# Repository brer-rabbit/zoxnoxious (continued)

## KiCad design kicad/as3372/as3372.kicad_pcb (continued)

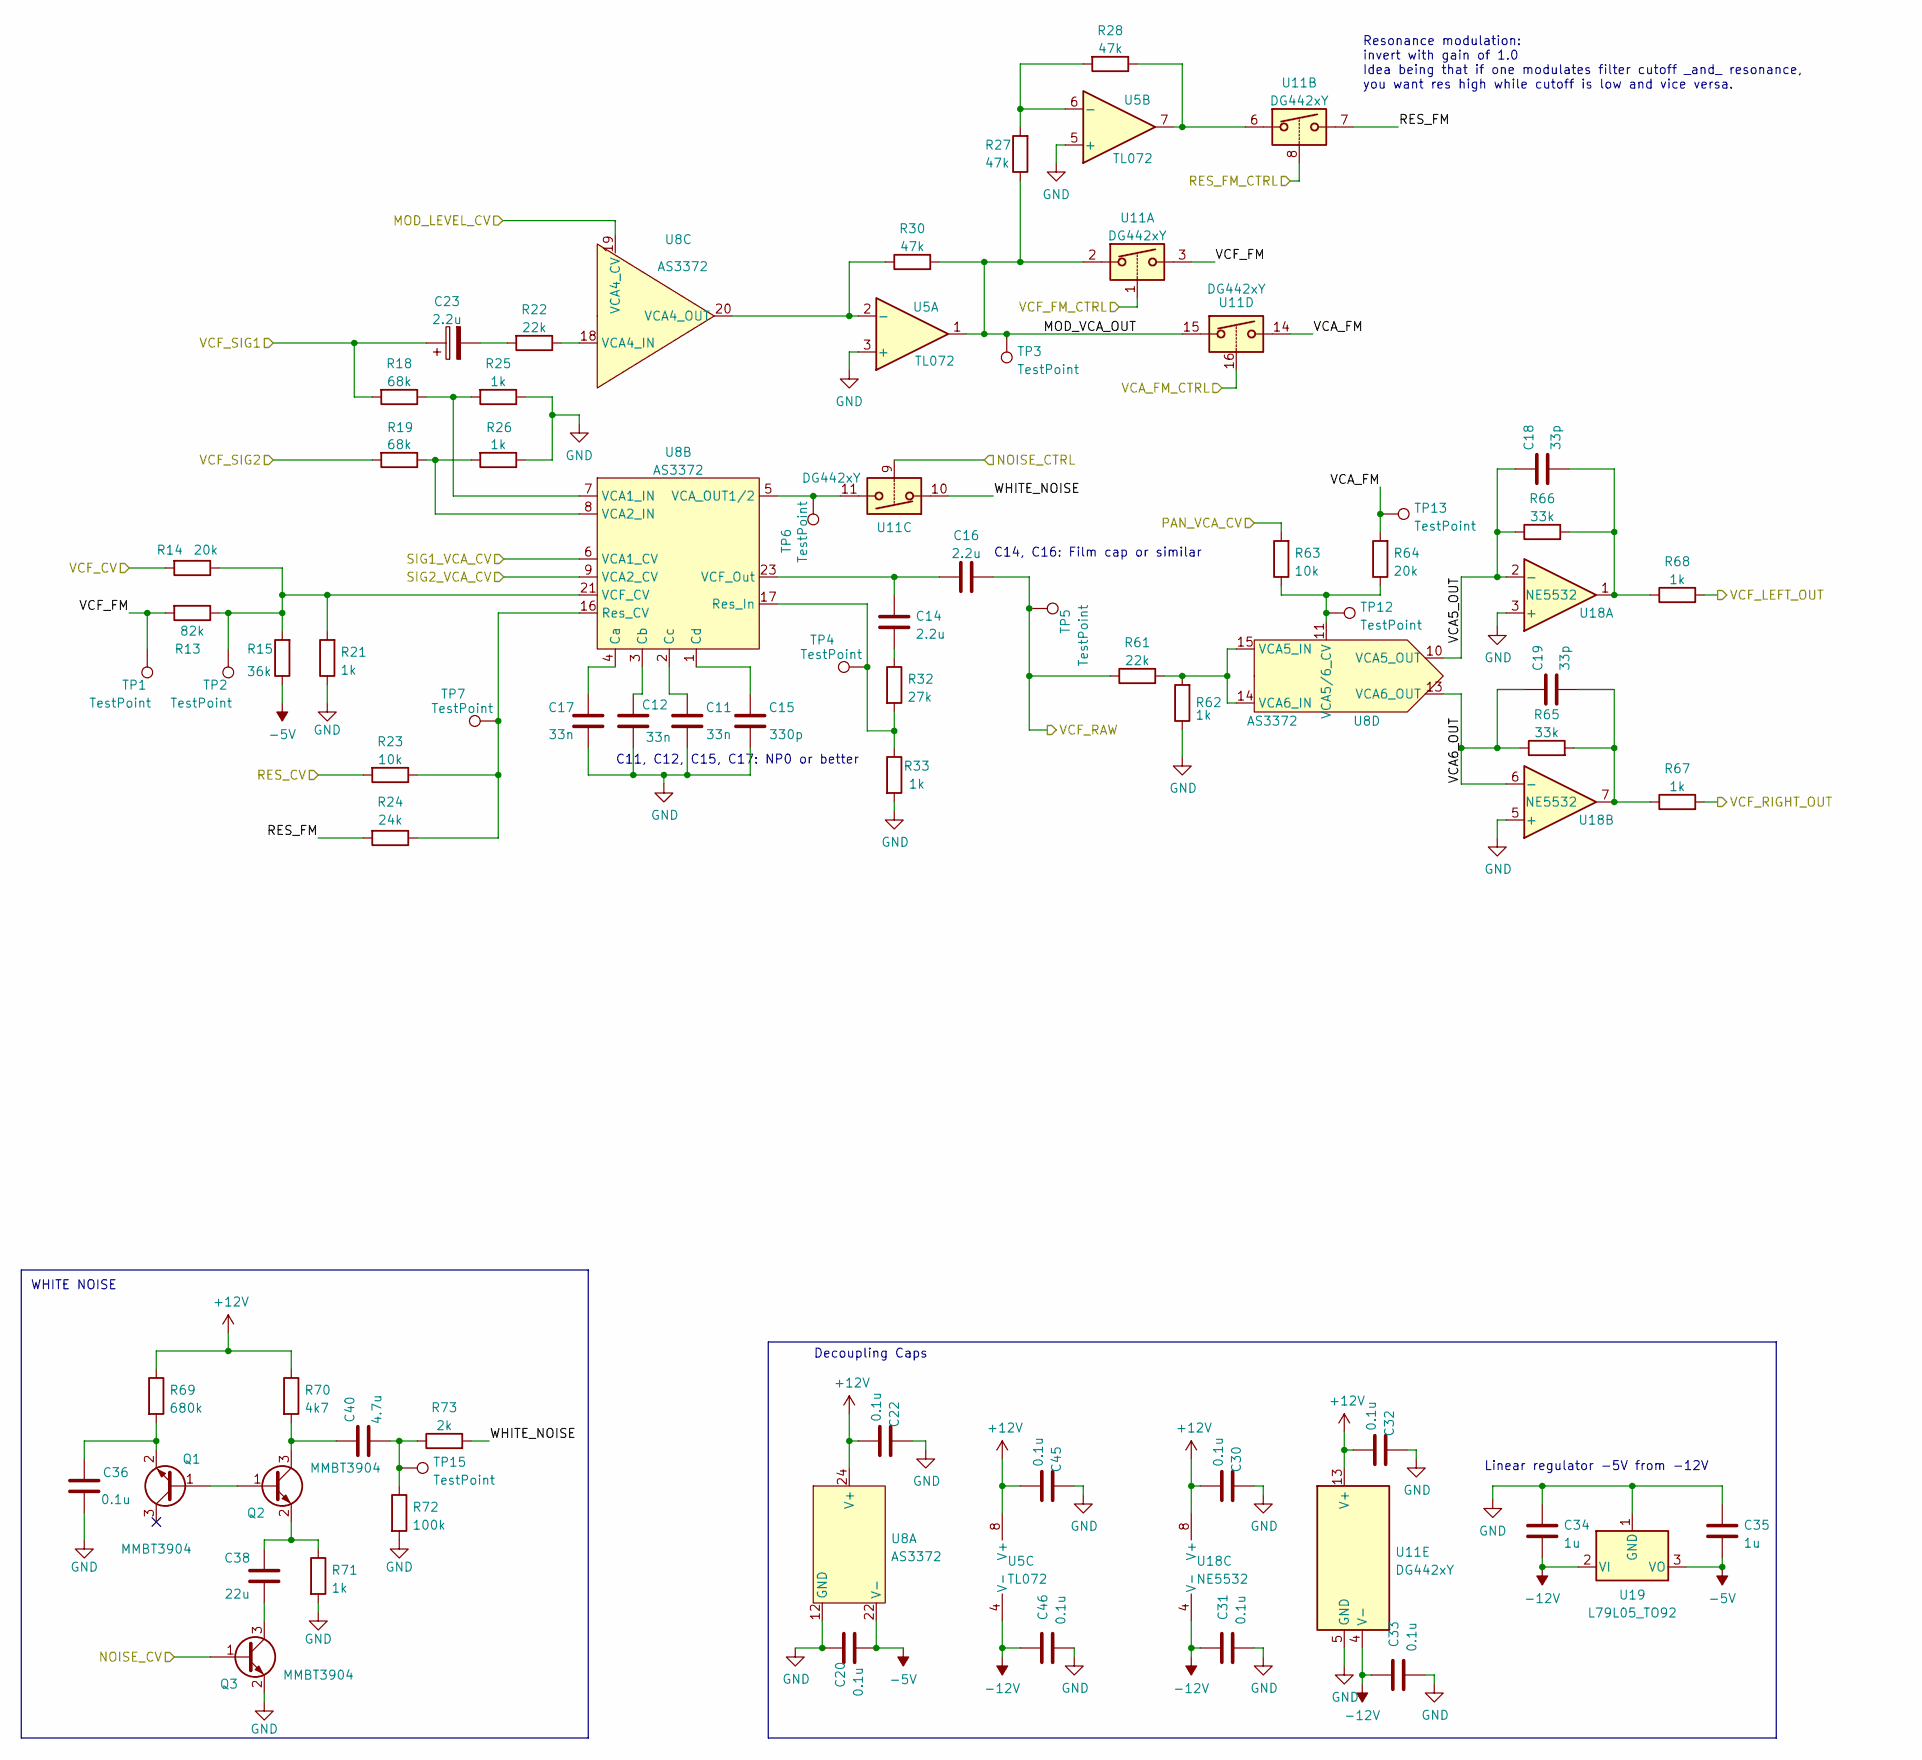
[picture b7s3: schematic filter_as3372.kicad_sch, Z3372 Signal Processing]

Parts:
C11, C12, C17: 33n; C_0805_2012Metric; LCSC Part C342800
C14, C16: 2.2u; C_Rect_L7.2mm_W5.5mm_P5.00mm_FKS2_FKP2_MKS2_MKP2; Digikey MKS2B042201F00KSSD
C15: 330p; C_0805_2012Metric; LCSC Part C694185
C18, C19: 33p; C_0603_1608Metric; LCSC Part C1663
C20, C22, C30, C31, C32, C33, C36, C45, C46: 0.1u; C_0603_1608Metric; LCSC Part C14663
C23: 2.2u; CP_Radial_D4.0mm_P1.50mm; Digikey 1189-4114-ND
C34, C35: 1u; C_0805_2012Metric; LCSC Part C28323
C38: 22u; C_1206_3216Metric; LCSC Part C12891
C40: 4.7u; C_0805_2012Metric; LCSC Part C1779
Q1, Q2, Q3: MMBT3904; SOT-23; LCSC Part C20526
R13: 82k; R_0603_1608Metric; LCSC Part C23254
R14, R64: 20k; R_0603_1608Metric; LCSC Part C4184
R15: 36k; R_0603_1608Metric; LCSC Part C23147
R18, R19: 68k; R_0603_1608Metric; LCSC Part C23231
R21, R25, R26, R33, R62, R67, R68, R71: 1k; R_0603_1608Metric; LCSC Part C21190
R22, R61: 22k; R_0603_1608Metric; LCSC Part C31850
R23, R63: 10k; R_0603_1608Metric; LCSC Part C25804
R24: 24k; R_0603_1608Metric; LCSC Part C23352
R27, R28, R30: 47k; R_0603_1608Metric; LCSC Part C25819
R32: 27k; R_0603_1608Metric; LCSC Part C22967
R65, R66: 33k; R_0603_1608Metric; LCSC Part C4216
R69: 680k; R_0603_1608Metric; LCSC Part C25822
R70: 4k7; R_0603_1608Metric; LCSC Part C23162
R72: 100k; R_0402_1005Metric; LCSC Part C25741
R73: 2k; R_0603_1608Metric; LCSC Part C22975
TP1, TP2, TP3, TP4, TP5, TP6, TP7, TP12, TP13, TP15: TestPoint; TestPoint_Pad_2.0x2.0mm
U5: TL072; SOIC-8_3.9x4.9mm_P1.27mm; LCSC Part C6961
U8: AS3372; SOIC-24W_7.5x15.4mm_P1.27mm
U11: DG442xY; SOIC-16_3.9x9.9mm_P1.27mm; LCSC Part C144269
U18: NE5532; SOIC-8_3.9x4.9mm_P1.27mm; LCSC Part C7426
U19: L79L05_TO92; TO-92_Inline_Wide

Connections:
+12V: C22.2, C30.2, C32.2, C45.2, R69.1, R70.1, U5.8 (V+), U8.24 (V+), U11.13 (V+), U18.8 (V+); also elsewhere on the board
-5V: C20.2, C35.2, R15.1, U8.22 (V-), U19.3 (VO)
-12V: C31.1, C33.1, C34.2, C46.1, U5.4 (V-), U11.4 (V-), U18.4 (V-), U19.2 (VI); also elsewhere on the board
/DAC/MOD_AMOUNT_VCA3_CV: U8.19 (VCA4_CV); also elsewhere on the board
/DAC/NOISE_CONTROL_CV: Q3.1 (B); also elsewhere on the board
/DAC/PAN_VCA_CV: R63.2; also elsewhere on the board
/DAC/RESONANCE_CV: R23.2; also elsewhere on the board
/DAC/SIG1_VCA1_CV: U8.6 (VCA1_CV); also elsewhere on the board
/DAC/SIG2_VCA2_CV: U8.9 (VCA2_CV); also elsewhere on the board
/DAC/VCF_CV: R14.2; also elsewhere on the board
/RES_FM_CTRL: U11.8; also elsewhere on the board
/THIS_OUT1: R68.2; also elsewhere on the board
/THIS_OUT2: R67.2; also elsewhere on the board
/VCA_FM_CTRL: U11.16; also elsewhere on the board
/VCF_FM_CTRL: U11.1; also elsewhere on the board
/VCF_RAW: C16.2, R61.1, TP5.1; also elsewhere on the board
/VCF_SIGNAL1: C23.1, R18.2; also elsewhere on the board
/VCF_SIGNAL2: R19.2; also elsewhere on the board
/WHITE_NOISE_CTRL: U11.9; also elsewhere on the board
/filter_as3372/MOD_VCA_OUT: R27.1, R30.2, TP3.1, U5.1, U11.2, U11.15
/filter_as3372/RES_FM: R24.2, U11.7
/filter_as3372/VCA5_OUT: C18.1, R66.1, U8.10 (VCA5_OUT), U18.2 (-)
/filter_as3372/VCA6_OUT: C19.1, R65.1, U8.13 (VCA6_OUT), U18.6 (-)
/filter_as3372/VCA_FM: R64.2, TP13.1, U11.14
/filter_as3372/VCF_FM: R13.2, TP1.1, U11.3
/filter_as3372/WHITE_NOISE: R73.2, U11.10
GND: C11.2, C12.2, C15.2, C17.1, C20.1, C22.1, C30.1, C31.2, C32.1, C33.2, C34.1, C35.1, C36.2, C45.1, C46.2, Q3.2 (E), R21.1, R25.1, R26.1, R33.2, R62.1, R71.2, R72.2, U5.3 (+), U5.5 (+), U8.12 (GND), U11.5 (GND), U18.3 (+), U18.5 (+), U19.1 (GND); also elsewhere on the board
unnamed: C11.1, U8.2 (Cc)
unnamed: C12.1, U8.3 (Cb)
unnamed: C14.1, C16.1, U8.23 (VCF_Out)
unnamed: C14.2, R32.1
unnamed: C15.1, U8.1 (Cd)
unnamed: C17.2, U8.4 (Ca)
unnamed: C18.2, R66.2, R68.1, U18.1
unnamed: C19.2, R65.2, R67.1, U18.7
unnamed: C23.2, R22.2
unnamed: C36.1, Q1.2 (E), R69.2
unnamed: C38.1, Q2.2 (E), R71.1
unnamed: C38.2, Q3.3 (C)
unnamed: C40.1, Q2.3 (C), R70.2
unnamed: C40.2, R72.1, R73.1, TP15.1
unnamed: Q1.1 (B), Q2.1 (B)
unnamed: R13.1, R14.1, R15.2, R21.2, TP2.1, U8.21 (VCF_CV)
unnamed: R18.1, R25.2, U8.7 (VCA1_IN)
unnamed: R19.1, R26.2, U8.8 (VCA2_IN)
unnamed: R22.1, U8.18 (VCA4_IN)
unnamed: R23.1, R24.1, TP7.1, U8.16 (Res_CV)
unnamed: R27.2, R28.2, U5.6 (-)
unnamed: R28.1, U5.7, U11.6
unnamed: R30.1, U5.2 (-), U8.20 (VCA4_OUT)
unnamed: R32.2, R33.1, TP4.1, U8.17 (Res_In)
unnamed: R61.2, R62.2, U8.14 (VCA6_IN), U8.15 (VCA5_IN)
unnamed: R63.1, R64.1, TP12.1, U8.11 (VCA5/6_CV)
unnamed: TP6.1, U8.5 (VCA_OUT1/2), U11.11

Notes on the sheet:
Resonance modulation: invert with gain of 1.0 Idea being that if one modulates filter cutoff _and_ resonance, you want res high while cutoff is low and vice versa.
Decoupling Caps
C14, C16: Film cap or similar
WHITE NOISE
Linear regulator -5V from -12V
C11, C12, C15, C17: NP0 or better

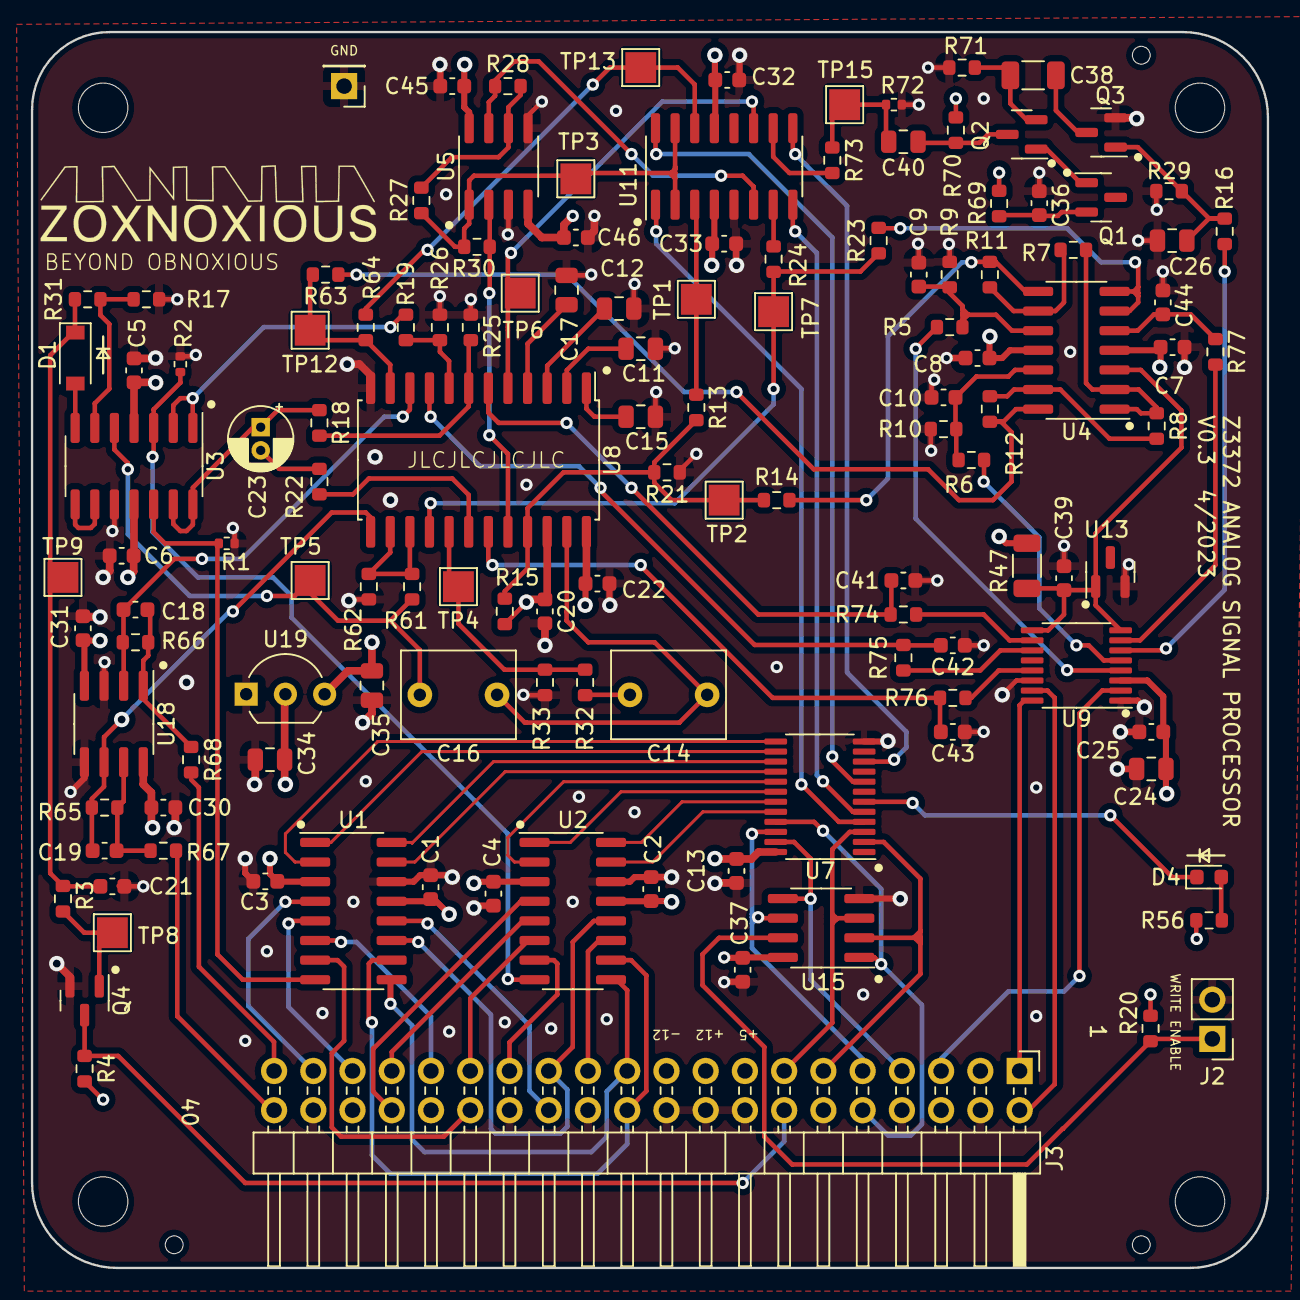
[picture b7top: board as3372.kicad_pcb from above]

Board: 4 copper layers, 80.0 x 80.0 mm, 133 parts (0 on the bottom side), 109 nets.

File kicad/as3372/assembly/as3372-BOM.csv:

Comment,Designator,Footprint,LCSC Part #
0.1u Unpolarized capacitor,"C1,C2,C3,C4,C5,C6,C7,C8,C13,C20,C21,C22,C25,C30,C31,C32,C33,C36,C37,C39,C45,C46",C_0603_1608Metric,C14663
68n Unpolarized capacitor,C9,C_0603_1608Metric,C31658
10n Unpolarized capacitor,"C10,C41,C42,C43,C44",C_0603_1608Metric,C57112
33n Unpolarized capacitor,"C11,C12,C17",C_0805_2012Metric,C342800
2.2u Unpolarized capacitor,"C14,C16",C_Rect_L7.2mm_W5.5mm_P5.00mm_FKS2_FKP2_MKS2_MKP2,
330p Unpolarized capacitor,C15,C_0805_2012Metric,C694185
33p Unpolarized capacitor,"C18,C19",C_0603_1608Metric,C1663
2.2u Polarized capacitor,C23,CP_Radial_D4.0mm_P1.50mm,
4.7u Unpolarized capacitor,"C24,C40",C_0805_2012Metric,C1779
22n Unpolarized capacitor,C26,C_0805_2012Metric,C21122
1u Unpolarized capacitor,"C34,C35",C_0805_2012Metric,C28323
22u Unpolarized capacitor,C38,C_1206_3216Metric,C12891
"1N4148W 75V 0.15A Fast Switching Diode, SOD-123",D1,D_SOD-123,C81598
LED Light emitting diode,D4,LED_0603_1608Metric,C2286
MountingHole Mounting Hole without connection,"H1,H2,H3,H4",MountingHole_3.2mm_M3,
"Conn_01x01 Generic connector, single row, 01x01, script generated (kicad-library-utils/schlib/autogen/connector/)",J1,PinHeader_1x01_P2.54mm_Vertical,
"Conn_01x02 Generic connector, single row, 01x02, script generated (kicad-library-utils/schlib/autogen/connector/)",J2,PinHeader_1x02_P2.54mm_Vertical,
"Conn_02x20_Odd_Even Generic connector, double row, 02x20, odd/even pin numbering scheme (row 1 odd numbers, row 2 even numbers), script generated (kicad-library-utils/schlib/autogen/connector/)",J3,PinHeader_2x20_P2.54mm_Horizontal,
"MMBT3904 0.2A Ic, 40V Vce, Small Signal NPN Transistor, SOT-23","Q1,Q2,Q3,Q4",SOT-23,C20526
100k Resistor,"R1,R2,R72",R_0402_1005Metric,C25741
4k7 Resistor,"R3,R20,R70",R_0603_1608Metric,C23162
10k Resistor,"R4,R23,R63",R_0603_1608Metric,C25804
2k4 Resistor,R5,R_0603_1608Metric,C22940
20k Resistor,"R6,R8,R10,R12,R14,R64",R_0603_1608Metric,C4184
8k2 Resistor,R7,R_0603_1608Metric,C25981
120k Resistor,R9,R_0603_1608Metric,C25808
3k3 Resistor,R11,R_0603_1608Metric,C22978
82k Resistor,R13,R_0603_1608Metric,C23254
36k Resistor,R15,R_0603_1608Metric,C23147
18k Resistor,R16,R_0603_1608Metric,C25810
100k Resistor,R17,R_0603_1608Metric,C25803
68k Resistor,"R18,R19",R_0603_1608Metric,C23231
1k Resistor,"R21,R25,R26,R33,R62,R67,R68,R71",R_0603_1608Metric,C21190
22k Resistor,"R22,R61",R_0603_1608Metric,C31850
24k Resistor,R24,R_0603_1608Metric,C23352
47k Resistor,"R27,R28,R30,R31",R_0603_1608Metric,C25819
9k1 Resistor,R29,R_0603_1608Metric,C23260
27k Resistor,R32,R_0603_1608Metric,C22967
4k7 Resistor,R47,R_1206_3216Metric,C17936
2k Resistor,"R56,R73",R_0603_1608Metric,C22975
33k Resistor,"R65,R66",R_0603_1608Metric,C4216
680k Resistor,R69,R_0603_1608Metric,C25822
15k Resistor,"R74,R75,R76,R77",R_0603_1608Metric,C22809
TestPoint test point,"TP1,TP2,TP3,TP4,TP5,TP6,TP7,TP8,TP9,TP12,TP13,TP15",TestPoint_Pad_2.0x2.0mm,
MUX508 ,"U1,U2",SOIC-16_3.9x9.9mm_P1.27mm,C2673104
"TL074 Quad Low-Noise JFET-Input Operational Amplifiers, DIP-14/SOIC-14","U3,U4",SOIC-14_3.9x8.7mm_P1.27mm,C12594
"TL072 Dual Low-Noise JFET-Input Operational Amplifiers, DIP-8/SOIC-8",U5,SOIC-8_3.9x4.9mm_P1.27mm,C6961
"CAT9555YI-T2 IO expander 16 GPIO, I2C 400kHz, Interrupt, 2.3 - 5.5V, SOIC-24",U7,TSSOP-24_4.4x7.8mm_P0.65mm,C83265
AS3372 AS 3372 Signal Processor,U8,SOIC-24W_7.5x15.4mm_P1.27mm,
AD5328 Octal Voltage Output DAC,U9,TSSOP-16_4.4x5mm_P0.65mm,C29162
"DG442xY Quad SPST Analog Switches, normally OFF, 60Ohm Ron, SOIC-16",U11,SOIC-16_3.9x9.9mm_P1.27mm,C144269
"LM4040AIM3-2.5 2.500V Precision Micropower Shunt Voltage Reference, SOT-23",U13,SOT-23,C460725
"M24C02-WMN 2Kb (256x8) I2C Serial EEPROM, 2.5-5.5V, SOIC-8",U15,SOIC-8_3.9x4.9mm_P1.27mm,C7562
"NE5532 Dual Low-Noise Operational Amplifiers, DIP-8/SOIC-8",U18,SOIC-8_3.9x4.9mm_P1.27mm,C7426
"L79L05_TO92 Negative 100mA -30V Linear Regulator, Fixed Output -5V, TO-92",U19,TO-92_Inline_Wide,

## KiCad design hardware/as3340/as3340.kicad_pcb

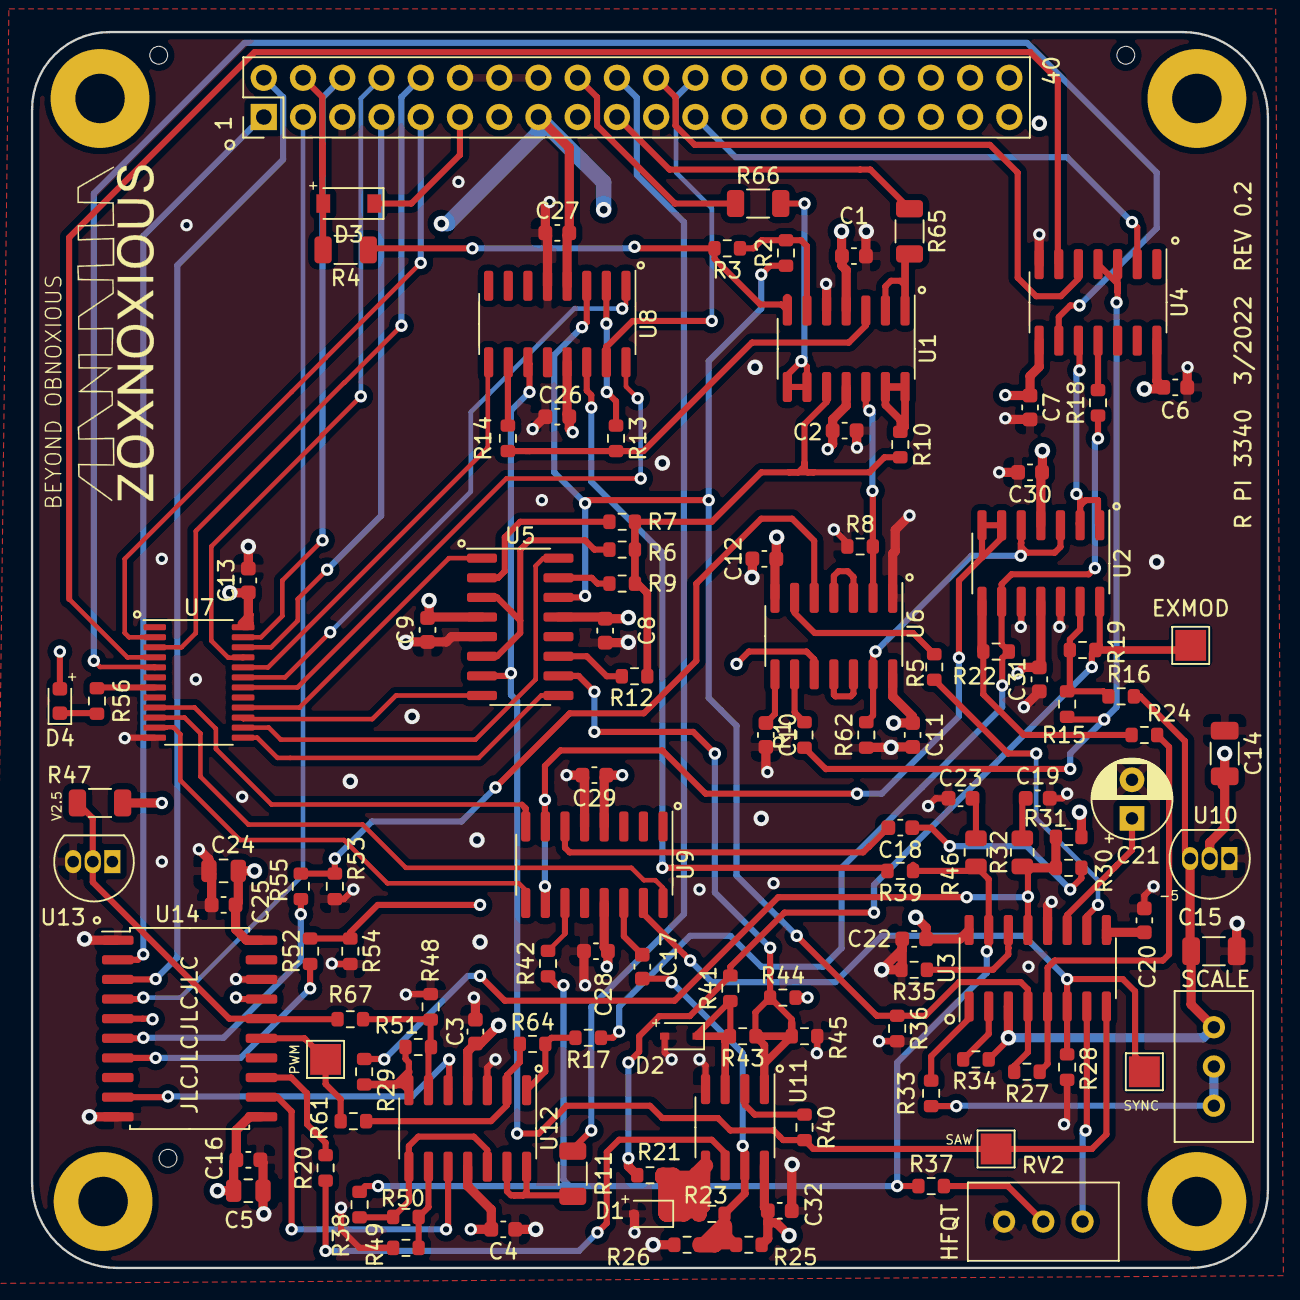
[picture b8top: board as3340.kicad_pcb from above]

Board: 4 copper layers, 80.0 x 80.0 mm, 123 parts (0 on the bottom side), 106 nets.

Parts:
C1, C2, C3, C4, C6, C7, C8, C9, C11, C12, C13, C22, C26, C27, C28, C29, C30, C31, C32: 0.1u; C_0603_1608Metric
C5, C24: 4.7u; C_0805_2012Metric
C10: 4.7n; C_0603_1608Metric
C14, C15: 1u; C_1206_3216Metric
C16, C20, C25: 100n; C_0603_1608Metric
C17: 1u; C_0603_1608Metric
C18, C19, C23: 10n; C_0603_1608Metric
C21: 1000p; CP_Radial_D5.0mm_P2.50mm
D1, D2: 1N5819; D_SOD-323
D3: 1N4148W; D_SOD-123
D4: LED; LED_0603_1608Metric
H1, H2, H3, H4: MountingHole; MountingHole_3.2mm_M3_Pad
J1: Conn_02x20_Odd_Even; PinHeader_2x20_P2.54mm_Vertical
R1, R2, R5, R6: 47k; R_0603_1608Metric
R3, R18, R48, R51: 100k; R_0603_1608Metric
R4, R11, R65, R66: 1k; R_1206_3216Metric
R7, R12, R14, R54, R55, R64: 20k; R_0603_1608Metric
R8, R62, R67: 51k; R_0603_1608Metric
R9, R13: 27k; R_0603_1608Metric
R10, R20, R21, R24, R28, R40, R41, R61: 10k; R_0603_1608Metric
R15, R16: 68k; R_0603_1608Metric
R17, R22: 56k; R_0603_1608Metric
R19: 33k; R_0603_1608Metric
R23, R27, R29, R30, R37, R43: 1M; R_0603_1608Metric
R25, R26, R34: 5k6; R_0603_1608Metric
R31: 1.5M; R_0603_1608Metric
R32, R46: 470; R_0805_2012Metric
R33: 20K; R_0603_1608Metric
R35: 1K82; R_0603_1608Metric
R36: 51K; R_0603_1608Metric
R38, R39: 100k 0.1%; R_0603_1608Metric
R42: 300k; R_0603_1608Metric
R44: 18k; R_0603_1608Metric
R45: 13k; R_0603_1608Metric
R47: 4k7; R_1206_3216Metric
R49: 10k .1%; R_0603_1608Metric
R50: 30k .1%; R_0603_1608Metric
R52, R53: 30k; R_0603_1608Metric
R56: 2k; R_0603_1608Metric
RV1: 10K; Potentiometer_Bourns_3296W_Vertical
RV2: 20k; Potentiometer_Bourns_3296W_Vertical
TP1, TP2, TP3, TP4: TestPoint; TestPoint_Pad_2.0x2.0mm
U1, U2, U12: TL074; SOIC-14_3.9x8.7mm_P1.27mm
U3: AS3340; SOIC-16_3.9x9.9mm_P1.27mm
U4: DG303B; SOIC-14_3.9x8.7mm_P1.27mm
U5, U8, U9: DG442CY+; SOIC-16_3.9x9.9mm_P1.27mm
U6: AS3360; SOIC-14_3.9x8.7mm_P1.27mm
U7: PCA9555D; TSSOP-24_4.4x7.8mm_P0.65mm
U10: LM79L05; TO-92_Inline
U11: LM393; SOIC-8_3.9x4.9mm_P1.27mm
U13: LM4040AIM3-5.0; TO-92L_Inline
U14: TLV5610IDW; SOIC-20W_7.5x12.8mm_P1.27mm

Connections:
+5V: C5.1, C13.1, C16.1, C24.2, C25.2, D3.1, D4.2, J1.11, R47.1, U7.24, U14.5, U14.11, U14.17, U14.20
+12V: C1.1, C3.1, C6.1, C8.1, C11.1, C22.2, C26.1, C28.1, C30.1, C32.1, J1.13, R25.2, R31.1, R44.2, U1.4, U2.4, U3.16, U4.14, U5.13, U6.14, U8.13, U9.13, U11.8, U12.4
-5V: C15.2, R16.2, R34.2, RV1.3, U3.3, U10.3
-12V: C2.2, C4.2, C7.2, C9.2, C12.2, C14.2, C27.2, C29.2, C31.2, J1.15, U1.11, U2.11, U4.8, U5.4, U6.7, U8.4, U9.4, U10.2, U12.11
/DAC/FREQ_CV_FROM_DAC: U12.10, U14.12
/DAC/LINEAR_FM_FROM_DAC: U12.5, U14.9
/DAC/OSC_EXT_VCA_FROM_DAC: R52.2, U14.7
/DAC/PWM_FROM_DAC: R61.2, TP1.1, U14.15
/DAC/TRI_VCA_FROM_DAC: R53.2, U14.6
/DAC/VREF_2.5V: R47.2, R67.2, U13.2, U14.16
/EXP_FM_EXT_CTRL: U7.11, U9.9
/EXT_CV: J1.24, U8.15
/EXT_FREQ_CV_CTRL: U7.18, U8.16
/EXT_MOD_PW_CTRL: U4.9, U7.5
/EXT_MOD_SEL_CTRL: U4.6, U7.4
/EXT_OSC_MOD: R1.1, R15.2, U4.3, U4.4
/EXT_OSC_VCA_AMOUNT: R52.1, R54.2, U6.10
/GPIO_MODULE_DRIVEN: D3.2, J1.4, R4.2
/GPIO_PI_DRIVEN: J1.3, U14.4
/HARD_SYNC_CTRL: U7.10, U9.16
/I2C_ADDR0: J1.8, U7.21
/I2C_ADDR1: J1.9, U7.2
/I2C_ADDR2: J1.10, U7.3
/LED_CTRL: R56.2, U7.7
/LINEAR_FM_DAC: R29.2, R51.1, U12.7
/LINEAR_FM_EXT_CTRL: U7.9, U9.8
/MIX1_COMP_OSC2_CTRL: U5.9, U7.13
/MIX1_PULSE_CTRL: U5.16, U7.14
/MIX1_SAW_CTRL: U5.8, U7.15
/MIX2_PULSE_CTRL: U7.19, U8.1
/MIX2_SAW_CTRL: U7.20, U8.9
/OSC1_CV: J1.20, R11.2
/OSC1_CV_DAC: R38.2, R50.1, U12.8, U12.12
/OSC1_MIX1: J1.18, R66.2
/OSC1_MIX2: J1.19, R65.2
/OSC2_MIX1: J1.22, U4.5
/OSC2_MIX2: J1.23, U4.2
/Output Mix/MIX1_SUM: R6.2, R7.2, R9.2, R10.2, R12.2, U1.10
/Output Mix/SCALED_TRI: R10.1, U1.13, U1.14
/Output Mix/VCA_TRI: R8.2, U1.12, U6.2
/PWM_DAC: R17.2, R64.1, U12.1
/SAW_LEVEL_CTRL: U5.1, U7.16
/SCL1: J1.7, U7.22
/SDA1: J1.6, U7.23
/SPI0_MOSI: J1.1, U14.2
/SPI0_SCLK: J1.2, U14.3
/SYNC_LEVEL_DAC: R20.2, U14.13
/TRI_VC_AMOUNT_DAC: R53.1, R55.2, U6.5
/VCO_COMP: R43.1, R44.1, R45.2, U5.10, U11.1
/VCO_PULSE: R2.1, R27.2, R36.1, U3.4, U5.14, U8.3
/VCO_SAW: R40.2, TP2.1, U3.8, U5.7, U8.11
/VCO_TRI: R5.1, U3.10
/cem3340/EXT_FREQ_CV: R39.2, U8.14
/cem3340/HARD_SYNC: R28.2, TP3.1, U3.6, U9.15
/cem3340/HIGH_FREQ_TRACK: RV2.1, U3.7
/cem3340/INV_SHIFTED_EXT_MOD: R19.1, R21.2, R41.2, TP4.1, U2.14
/cem3340/LINEAR_FM: R29.1, R30.1, R31.2, R32.1, U3.13
/cem3340/PWM: R24.1, R27.1, U3.5
/cem3340/SCALED_EXT_MOD: R62.2, U2.3, U2.5, U6.13
/cem3340/SCALED_MOD_BUFFERED: U2.6, U2.7, U9.7, U9.10
/cem3340/SOFT_SYNC: C20.1, U3.9
/cem3340/SUMMING_INPUT: R37.1, R38.1, R39.1, R42.1, R46.1, U3.15
GND: C1.2, C2.1, C3.2, C4.1, C5.2, C6.2, C7.1, C8.2, C9.1, C10.2, C11.2, C12.1, C13.2, C14.1, C15.1, C16.2, C19.2, C20.2, C21.2, C22.1, C23.2, C24.1, C25.1, C26.2, C27.1, C28.2, C29.1, C30.2, C31.1, C32.2, D1.2, D2.2, J1.5, J1.12, J1.14, J1.16, J1.17, J1.21, J1.25, J1.28, J1.31, J1.34, R8.1, R26.1, R28.1, R35.2, R36.2, R45.1, R48.1, R49.2, R54.1, R55.1, R62.1, RV2.3, U1.5, U2.10, U2.12, U3.12, U4.7, U5.5, U6.1, U7.12, U8.5, U9.5, U10.1, U11.4, U12.3, U13.3, U14.1, U14.10, U14.18
unnamed: C10.1, U6.8
unnamed: C17.1, U9.14
unnamed: C17.2, R23.1, R25.1, R26.2, U11.7
unnamed: C18.1, R30.2
unnamed: C18.2, U9.6
unnamed: C19.1, R32.2
unnamed: C21.1, U3.11
unnamed: C23.1, R46.2
unnamed: D1.1, R21.1, R23.2, U11.5
unnamed: D2.1, R41.1, R43.2, U11.3
unnamed: D4.1, R56.1
unnamed: R1.2, U6.9
unnamed: R2.2, R3.1, U1.6
unnamed: R3.2, R4.1, U1.7
unnamed: R5.2, U6.6
unnamed: R6.1, U5.3, U5.6
unnamed: R7.1, U5.2
unnamed: R9.1, U5.15
unnamed: R11.1, U12.13, U12.14
unnamed: R12.1, U5.11
unnamed: R13.1, U8.2
unnamed: R13.2, R14.2, U1.3
unnamed: R14.1, U8.10
unnamed: R15.1, R16.1, R19.2, U2.13
unnamed: R17.1, R18.1, R22.2, U2.9
unnamed: R18.2, U4.11
unnamed: R20.1, U11.6
unnamed: R22.1, R24.2, U2.8
unnamed: R33.1, U3.1
unnamed: R33.2, RV1.1, RV1.2
unnamed: R34.1, U3.2
unnamed: R35.1, U3.14
unnamed: R37.2, RV2.2
unnamed: R40.1, U11.2
unnamed: R42.2, U9.11
unnamed: R48.2, R51.2, R67.1, U12.6
unnamed: R49.1, R50.2, U12.9
unnamed: R61.1, R64.2, U12.2
unnamed: R65.1, U1.1, U1.2
unnamed: R66.1, U1.8, U1.9
unnamed: U2.1, U2.2, U4.10
unnamed: U6.3, U6.4
unnamed: U6.11, U6.12

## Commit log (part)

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2024-10-14 getting through autotune routines
2024-10-15 tuning updates for z3372
2024-10-21 add 3372 datasheet and move 3340 sheet
2024-10-24 tuning should work on z3372 now
2024-10-24 fix spi mode stuff that was used for caching
2024-11-04 some initial rantings on the poledancer schematic. Lots of work to do to figure out resonance and 2190 integration
2024-11-05 crazy ideas on resonance compensation
2024-11-08 think I got rez phase correct now. Still working on exp input circuit
2024-11-14 schematic about ready for review. Need GPIO out still. then review.
2024-11-15 change direction on which pole to use with VCA. Trying it out
2024-11-16 ditch moving the VCA cell to last position, keep it in position 2. More VCA mode offered that way. Other change is adding all JLCPCB components to fields
2024-11-17 figured a few things out after breadboarding 2190. Bigger R values for signals.
2024-11-19 create hand solder footprints for SSI chips. Get some placement done.
2024-11-22 updated rez comp mode. Back to placement on PCB.
2024-11-23 continue placement
2024-11-24 a bit more tweaking on placement
2024-11-25 swap some instances around for better routing
2024-11-27 start routing power
2024-11-27 poledancer: zero unrouted! now to de-uglify the routing
2024-11-29 cleaning up reference designators
2024-11-29 move some designtors, add some ground vias, cleanup
2024-12-01 v0.1 sent to manufacture
2024-12-02 correct out1 vs out2 labels in Z3372 Rack
2024-12-04 pi pole dancer driver untested checkin
2024-12-05 swap z3372 rack out1 and out2
2024-12-09 start a VCV Rack Pole Dancer module
2024-12-12 got something in VCV that might work for Pole Dancer
2024-12-12 typo in comment fix
2024-12-13 add button lights to Rack and fix RPi Pole Dancer driver
2024-12-13 poledancer rpi config
2024-12-13 add channel offset for cs1
2024-12-13 correct the methods for knob vs input processing
2024-12-14 change how chip select 1 DAC references samples
2024-12-15 provide poly input for pole mix levels
2024-12-18 fix label error between pole2/pole4 in DAC channels in schematic. no layout change.
2024-12-18 update Rack & Pi drivers for pole4/pole2 swap
2024-12-22 change cv channels from magic numbers to enum references used as ints
2024-12-23 basic for UI to limit pulse width in Z5524 via VCV Rack
2024-12-30 patching matrix update for non-copy of audio frame
2024-12-30 better comment update on rez comp
2025-01-01 increase width of text boxes for readability
2025-01-01 text field works, still have annoying grey bounding box lines
2025-01-02 untested tuning code for poledancer
2025-01-02 pole dancer now has cpu autotuning
2025-01-02 presets added to PoleDancer Personality VCV Rack module
2025-01-03 change Pole Dancer Rack interface to set of Rez compensation modes
2025-01-03 tweak resonance curve on poledancer for various rez comp modes
2025-01-05 set rezcomp mode string from JSON
2025-01-06 Rack: set rez to half since Pi PoleDancer drive is operating at 2X gain
2025-01-14 change all Personality presets to 8x gain
2025-01-19 resolve issue of source one getting a bad midi program change on startup
2025-02-03 updates for v0.5. Fix range for autotune. Noise level improved. Modulation range increased.
2025-02-06 checkpoint for z3340 v0.9. Fixed lm4040 resistor, exp modulation level; removed polygons from routing
2025-02-07 updates for v0.9: polygons, LED resistor, mod amount
2025-02-11 changed linear mod amount for z3340, from tame to wild now. Updated poledancer 2140, better DAC RC filter (higher freq) for 2190.
2025-02-13 updates to z3340 and poledancer schematics and layout
2025-02-14 Release ready files for Pole Dancer v0.2
2025-02-18 update z5524 title block
2025-03-07 updated gerber files for pole dancer and updated tooling holes for all designs
2025-03-11 updated z5524 gerber files: RTM v0.5
2025-03-31 change midi thread to use poll() with timeout
2025-04-01 zoxnoxiousd pi app: Up SPI rate to 30Mhz (though my scope shows it at 50Mhz). Add mlockall() to ensure pages locked in main memory. Change buffer sizes to account for 8kHz sampling rate. That's right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
2025-04-01 improved posix signal handling
2025-04-03 better handling of system restart/shutdown. Clean is done first then the action is taken by the main thread.
2025-04-04 add youtube deep dive video to README
2025-04-06 add z3340 block diagram
2025-04-06 typo
2025-04-06 readme files and resources for all kicad voice cards
2025-04-22 schematic for backplane v0.3: change Pi GPIOs for SPI; switch output jacks; add external input
2025-04-26 starting on placement
2025-05-04 remap some pins
2025-05-19 add external input sheet. Basic routing on backplane done- needs cleaning up
2025-05-20 cleanup in progress- looking to change how the SPI lines are buffered
2025-05-21 geographically reorientated from pcb
2025-05-30 minor update
2025-06-20 checkin before moving pi footprint a bit
2025-06-25 RTM backplane/VCA board v0.3
2025-06-25 close kicad project/sync
2025-08-19 update pi gpio and i2c gpio for v0.3 backplane
2025-09-06 update AudioIO for VCV Rack for bugfix from 1-6 channels twice
2025-09-08 add AudioIO RPi lib
2025-10-12 front panel v1.0 to production
2025-10-31 initial z2203 schematic
2025-11-19 move some stuff around for some minor changes. The 2203 WR looks fine based on Capcom's Commando schematics
2025-11-22 silkscreen updates
2025-11-27 add testpoints to DAC2190 for calibration
2025-12-05 update title blocks
2025-12-09 add readme for kicad
2025-12-19 add vca calibration files and start integrating with poledancer pi driver
2025-12-30 calloc args were reversed...and that worked for how long?
2026-01-02 updated datasheet for z3340 card
2026-01-06 replace printf with zlog info/warn/error messages
2026-01-07 remove backup files
2026-01-07 AudioIO VCV Rack hardware to match Pi driver
2026-01-10 VCA calibration code near final cleanup. Remove logging statements, minor optimization in init function
2026-01-14 free calibration data on close
2026-01-15 correctly free VCA DAC calibration memory
2026-01-18 allow startup when cards EEPROM is uninitialized, skipping that card
2026-01-28 change gpioWrite() calls to gpioWrite_Bits_0_31_Set/Clear(). Reduces gpio calls from 3 to 2 for every slot change which could be eight calls in 250us.
2026-02-05 split adapter to cpp/hpp
2026-02-06 split Audio header/impl
2026-02-08 attach lights working. Formatting across files/indentation fixed.
2026-02-10 better names for constants, portable INFO statements, debating how to handoff discovery report
2026-02-10 add registerDevices skeleton method
2026-02-11 add ignore of Discovery Report after first one
2026-02-12 set published in registerDevices, allowing participant registration
2026-02-12 correct clock divider handling
2026-02-13 add lights back in to z3340
2026-02-14 introduce ButtonMidiController -- work in progress
2026-02-14 better names, include buttonmidicontr to z3340
2026-02-16 working button midi controller. Shift focus back to getting midi + CVs working
2026-02-17 cleanup: midi sysex messages were fixed so made them static
2026-02-17 get midi messages sent to orchestrator
2026-02-17 move initializer list to member defaults
2026-02-17 selector lights active for a frame on push
2026-02-23 control voltages added to output frame, frame output to devices
2026-02-24 add more rez comp modes for test
2026-02-25 add slot number to participant properties. Fix bug in 3340 selector / num cards
2026-03-02 add HardwareNameService. Remove all strings from AudioIO module; in ui ModuleWidget only now
2026-03-04 participant modules now get their slot info and access to name strings
2026-03-05 fix indentation
2026-03-11 decoupled architecture now works. Moved attach responsibility to AudioIO orchestrator. Detach still initiated by module. We'll see how that works out
2026-03-13 add heartbeat and detach process. Start to rebuild PoleDancer with new Participant structure
2026-03-13 Pole Dancer dancing and sending MIDI messages
2026-03-13 start using CvRoute helper
2026-03-14 use CV route helper
2026-03-16 nasty index bug where a skipped slot screws things up
2026-03-16 fix DC offset limit on 5524 VCO2
2026-03-18 finish refactor with Z3372. Pull out common code for refactor as well
2026-04-06 updated panels for z3340
2026-04-10 updated layout for z3340
2026-04-16 columns finally feeling solid on z3340
2026-04-16 column layout about there
2026-04-17 label tracking adjustment
2026-04-20 minor touch
2026-04-20 oh yeah- DSEG14 bold italic. spot on.
2026-04-20 cleanup
2026-04-21 update shading
2026-04-21 some basic turns counting knob stuff. Not much decoration
2026-04-22 add fg/bg to dial
2026-04-22 wrong branch
2026-04-23 add shadow for inner knob
2026-04-24 visual on the turn counter knob- looking a lot better
2026-04-24 add slight gradient
2026-04-25 various tweeks to get the BNC a bit more rack-realistic
2026-04-27 pretty much final here-- looking good
2026-04-27 tweaks to center right side column
2026-04-30 allow add or mult for typical knob and jack combo
2026-04-30 fix normalled behavior to actual VCA like. Com Status --> Module Link
2026-05-02 update SVG to recent working copy of Output Interface
2026-05-02 better handling for strings in registry
2026-05-02 refactor common.hpp to constants and modulehelpers
2026-05-05 add a small push button. Remove legacy small VCV Rack button.
2026-05-05 better contrast on arrows
2026-05-05 fix duplicate datasheet files for z3340
2026-05-08 rename AudioIO to OutputInterface
2026-05-08 remove old AudioOut SVGs
2026-05-12 adding Peeping Tom module: a visualizer for the Pole Dancer filter coefs
2026-05-13 turns counting dial to zox namespace
2026-05-14 fix incorrect slots reported in patch usage LEDs
2026-05-16 pretty solid 5524 panel
2026-05-16 add light logic for tzfm/waveshape status LEDs; change first output to VOICE
2026-05-16 silkscreen update: VCA --> VOICE
2026-05-18 drop expander name from status light
2026-05-18 starting pole dancer re-skin
2026-05-19 add small directional push buttons. Update PD with these
2026-05-21 minor text change
2026-05-21 Personality can now add analyzer via right-click menu
2026-05-21 code fixes from review
2026-05-21 add workbench svg file
2026-05-21 identifier name changes for better clarity
2026-05-22 workbench complete. template-kind of.
2026-05-22 Personality module is doing good
2026-05-22 add alternate workbench svg for personality
2026-05-22 minor cleanup
2026-05-23 drop DIN1451 due to license. Pickup OSP-DIN
2026-05-23 label update
2026-05-23 add thumbscrew hardware (forgot, oops) and some label updates
2026-05-23 strengthen a couple lines in the workbench display
2026-05-24 center up mid-lane on Pole Dancer. Add other resonance modes
2026-05-28 updated Z3340 layout for the better. Z3372 is at a pivot point: about to try different design
2026-05-29 good looking z3372!
2026-05-29 increase business section on TurnsCountingDial
2026-05-29 move the pole mix scale factor to a constant
2026-05-31 add new knob types
2026-06-01 slug change for VCV Rack hardware modules. sigh.
2026-06-01 add new knobs to panels
2026-06-05 really cool visual on z5524 modulation
2026-06-06 update labels on visualizer
2026-06-07 visualizer is golden
2026-06-08 knob scales should show 8X
2026-06-08 add right-click for visualizer on 5524
2026-06-10 fix tooltip typo; change VCA knobs+jack combo to normalled multiply
2026-06-11 break out TZFM raw/shaped. Different color.
2026-06-14 start hardware discovery branch
2026-06-15 create skeleton visualizer module. Change expander interface to fixed length arrays
2026-06-15 move dump of graph to visualizer, showing the data structs make it to the expander
2026-06-16 some basic working visuals
2026-06-17 creating the graph data structs now on solid ground
2026-06-17 some layout improvements
2026-06-18 checkpoint
2026-06-19 minor refactor
2026-06-20 start playing with weights -- and it's completely wrong right now
2026-06-20 add weight for output interface
2026-06-20 got weights added almost everywhere- dual voice still todo
2026-06-21 starting some cleanup
2026-06-21 somehow "clip" moved. moving it back.
2026-06-22 forgot one thing
2026-06-25 node column/row placement is on firm ground
2026-06-27 double buffer struct to UI. Orthogonal routing added; needs some refinement
